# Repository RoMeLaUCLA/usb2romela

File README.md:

# USB2RoMeLa RS-485 USB Adapter

USB2RoMeLa Boosted is a low latency USB to RS-485 adapter. FT232H is used for USB to serial conversion. STM32 intercepts data packets and signals FT232H whenever a complete data packet is received, lowering roundtrip communication latency.
Packet acceleration is designed around Dynamixel communication protocols. 

 ## System Diagram

# Usage

## Baudrate setting

## Terminal resistor setting

## Startup code
 - Flash 2 times: 8Mbps
 - Flash 3 times: 3Mbps
## Error code 
 - Flash 1 time: Packet Timeout
 - Flash 2 times: Checksum Error
 - Flash 3 times: UART Error

# PCB reference

[Link to schematics](/pcb/USB2RoMeLa_Boosted_rev2_1.pdf)

# Latency test

# Folder structure

cad: 3D CAD files and render.

firmware: STM32 firmware with STM32CubeIDE project. \
firmware\Bin: binary file of compiled firmware.

pcb: PCB design files(KiCAD) and schematics. \
pcb\BOM: Bill of Materials. \
pcb\Gerber: PCB mfg files.

tools\ftdi-template: template to use when programing FT232H using FT_Prog.

tools\programming-interface-pcb: PCB design files for interface board with castellation.

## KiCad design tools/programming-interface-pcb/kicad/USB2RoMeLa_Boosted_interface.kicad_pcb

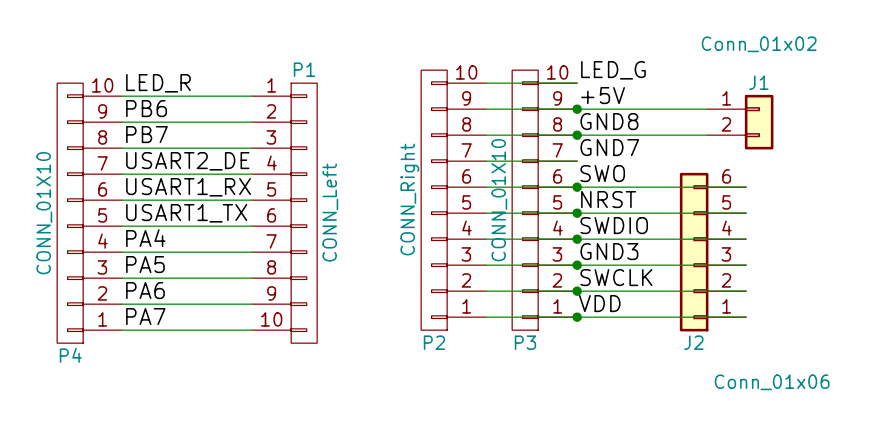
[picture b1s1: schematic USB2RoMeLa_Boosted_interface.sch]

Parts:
J1: Conn_01x02; Molex_MiniFit-JR-5556-02A_2x01x4.20mm_Straight
J2: Conn_01x06; JST_SH_SM06B-SRSS-TB_06x1.00mm_Angled
P1: CONN_Left; Spring_Contact_10P
P2: CONN_Right; Spring_Contact_10P
P3, P4: CONN_01X10; Socket_Strip_Straight_1x10_Pitch2.54mm

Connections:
/+5V: J1.1, P2.9, P3.9
/GND3: J2.3, P2.3, P3.3
/GND7: P2.7, P3.7
/GND8: J1.2, P2.8, P3.8
/LED_G: P2.10, P3.10
/LED_R: P1.1, P4.10
/NRST: J2.5, P2.5, P3.5
/PA4: P1.7, P4.4
/PA5: P1.8, P4.3
/PA6: P1.9, P4.2
/PA7: P1.10, P4.1
/PB6: P1.2, P4.9
/PB7: P1.3, P4.8
/SWCLK: J2.2, P2.2, P3.2
/SWDIO: J2.4, P2.4, P3.4
/SWO: J2.6, P2.6, P3.6
/USART1_RX: P1.5, P4.6
/USART1_TX: P1.6, P4.5
/USART2_DE: P1.4, P4.7
/VDD: J2.1, P2.1, P3.1

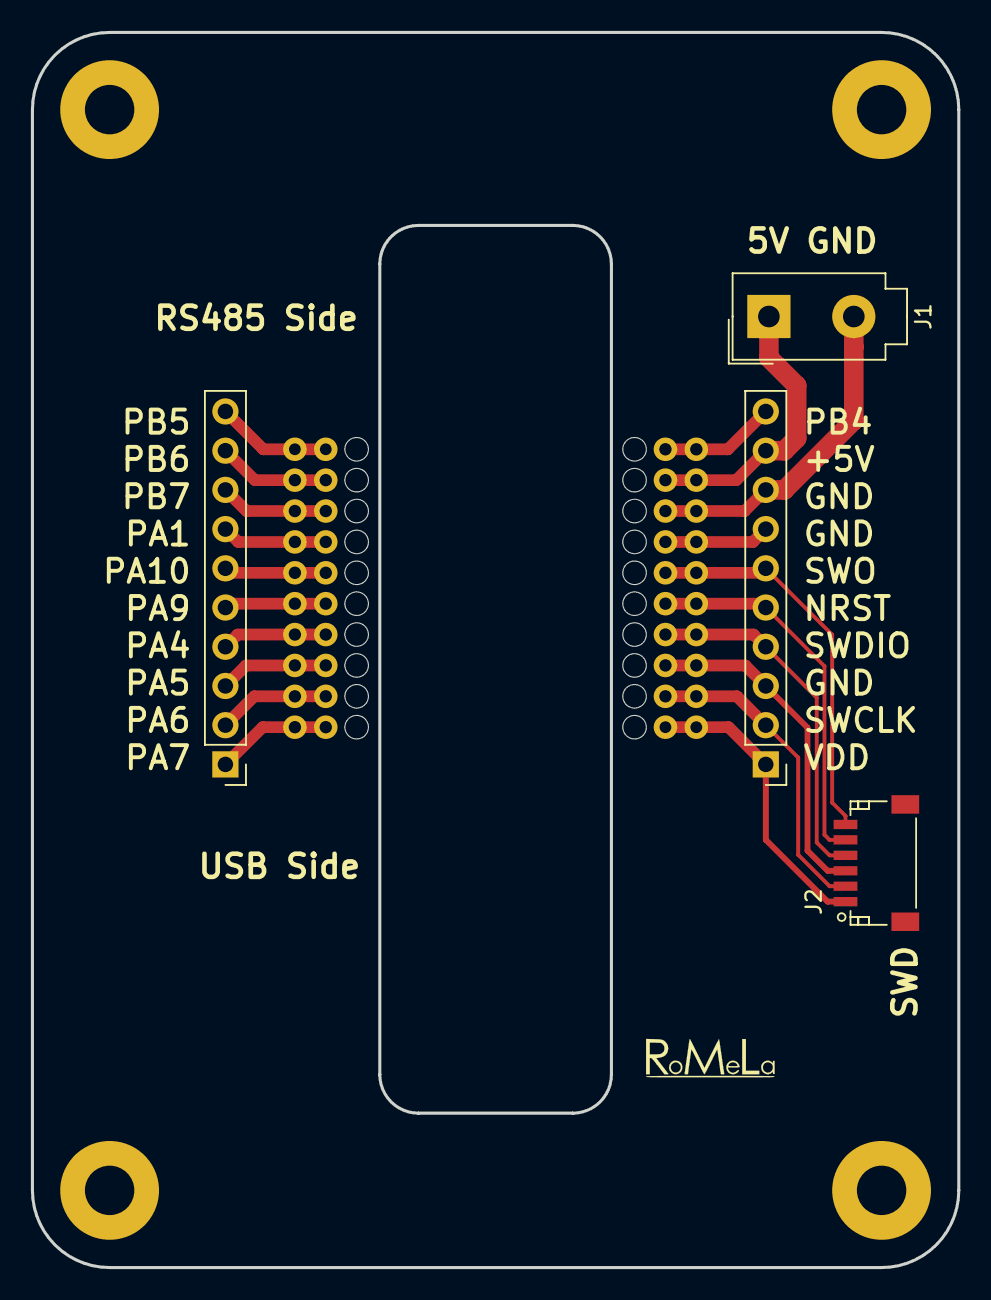
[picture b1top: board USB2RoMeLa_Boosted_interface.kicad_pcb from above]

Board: 2 copper layers, 60.0 x 80.0 mm, 6 parts (0 on the bottom side), 20 nets.

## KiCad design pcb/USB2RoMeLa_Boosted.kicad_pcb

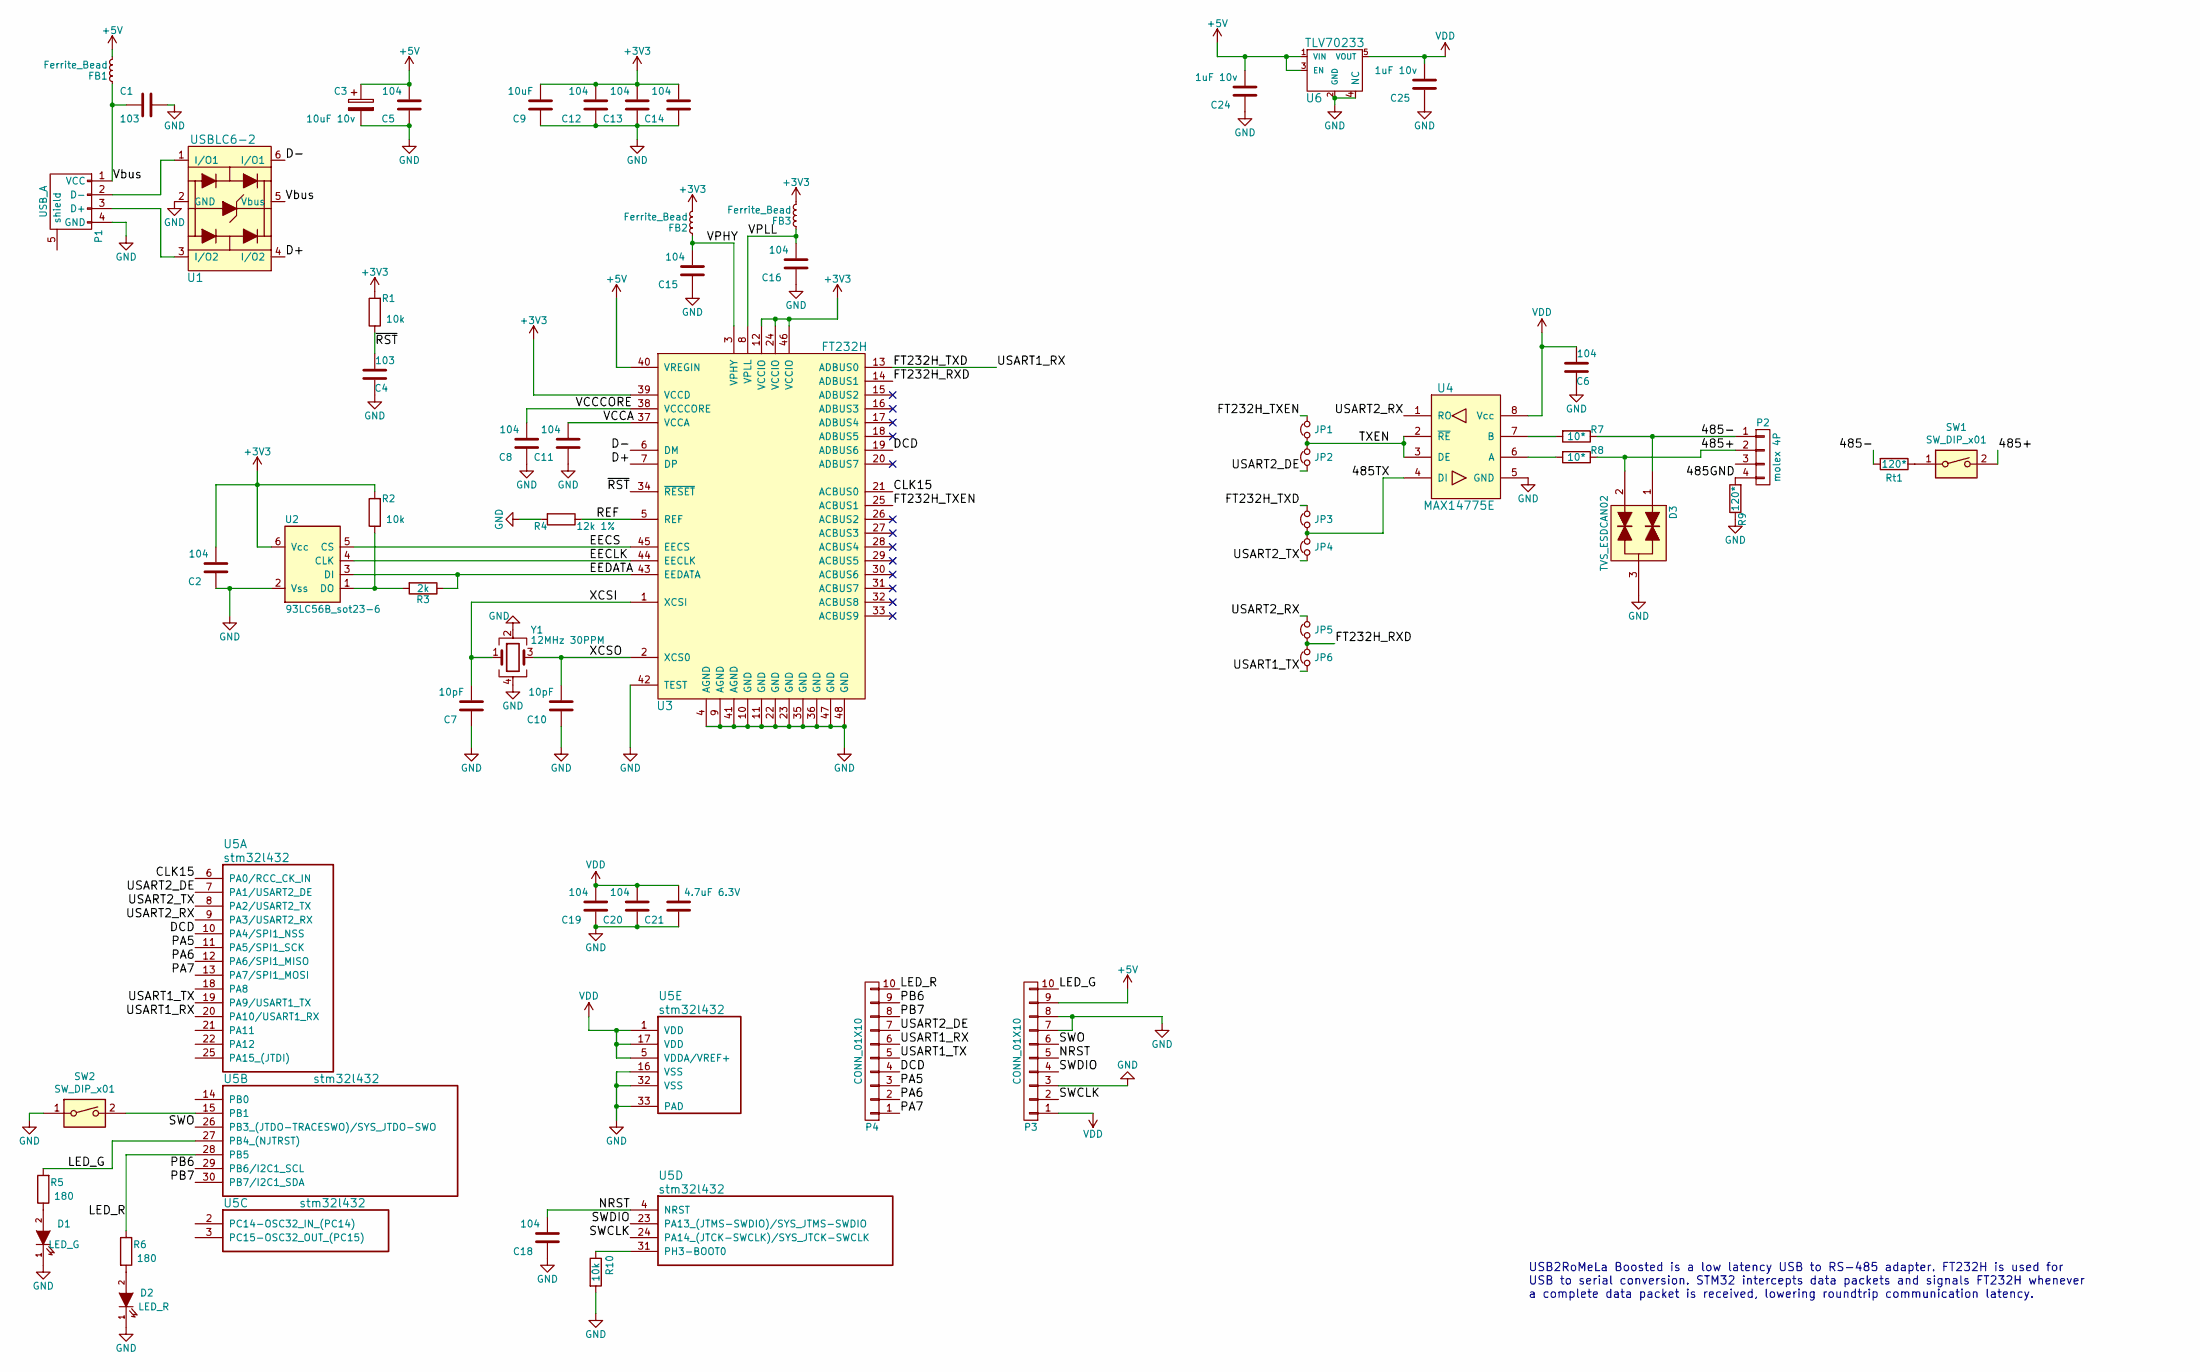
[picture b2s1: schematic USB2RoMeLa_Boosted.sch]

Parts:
C1, C4: 103; C_0402_1005Metric
C2, C5, C6, C8, C11, C12, C13, C14, C15, C16, C18, C19, C20: 104; C_0402_1005Metric
C3: 10uF 10v; C_0805_2012Metric
C7, C10: 10pF; C_0402_1005Metric
C9: 10uF; C_0805_2012Metric
C21: 4.7uF 6.3V; C_0805_2012Metric
C24, C25: 1uF 10v; C_0603_1608Metric
D1: LED_G; LED_0603_1608Metric
D2: LED_R; LED_0603_1608Metric
D3: TVS_ESDCAN02; SOT-323_SC-70
FB1, FB2, FB3: Ferrite_Bead; R_0402_1005Metric
JP1, JP2, JP3, JP4, JP5, JP6: Jumper_NC_Small; R_0402_1005Metric
P1: USB_A; USB_typeA_TH
P2: molex 4P; Molex_4P
P3, P4: CONN_01X10; castellation_10P_2mm
R1, R2, R10: 10k; R_0402_1005Metric
R3: 2k; R_0402_1005Metric
R4: 12k 1%; R_0402_1005Metric
R5, R6: 180; R_0603_1608Metric
R7, R8: 10*; R_0603_1608Metric
R9: 120*; R_0805_2012Metric
Rt1: 120*; R_0805_2012Metric
SW1, SW2: SW_DIP_x01; SW_DIP_SPSTx01_Slide_Copal_CHS-01A_W5.08mm_P1.27mm_JPin
U1: USBLC6-2; SOT-23-6
U2: 93LC56B_sot23-6; SOT-23-6
U3: FT232H; LQFP-48_7x7mm_P0.5mm
U4: MAX14775E; SOIC-8_3.9x4.9mm_P1.27mm
U5: stm32l432; VQFN-32-1EP_5x5mm_P0.5mm_EP3.5x3.5mm
U6: TLV70233; SOT-23-5
Y1: 12MHz 30PPM; Crystal_SMD_2520-4Pin_2.5x2.0mm

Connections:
+3V3: C2.2, C9.2, C12.2, C13.2, C14.2, FB2.2, FB3.2, R1.2, R2.2, U2.6 (Vcc), U3.12 (VCCIO), U3.24 (VCCIO), U3.39 (VCCD), U3.46 (VCCIO)
+5V: C3.1, C5.2, C24.2, FB1.2, P3.9, U3.40 (VREGIN), U6.1 (VIN), U6.3 (EN)
/485+: D3.2, P2.2, R8.1, SW1.2
/485-: D3.1, P2.1, R7.1, Rt1.2
/485GND: P2.4, R9.2
/485TX: JP3.1, JP4.2, U4.4 (DI)
/CLK15: U3.21 (ACBUS0), U5.6 (PA0/RCC_CK_IN)
/D+: U1.4 (I/O2), U3.7 (DP)
/D-: U1.6 (I/O1), U3.6 (DM)
/DCD: P4.4, U3.19 (ADBUS6), U5.10 (PA4/SPI1_NSS)
/EECLK: U2.4 (CLK), U3.44 (EECLK)
/EECS: U2.5 (CS), U3.45 (EECS)
/EEDATA: R3.1, U2.3 (DI), U3.43 (EEDATA)
/FT232H_RXD: JP5.1, JP6.2, U3.14 (ADBUS1)
/FT232H_TXD: JP3.2, P4.6, U3.13 (ADBUS0), U5.20 (PA10/USART1_RX)
/FT232H_TXEN: JP1.2, U3.25 (ACBUS1)
/LED_G: P3.10, R5.2, U5.27 (PB4_(NJTRST))
/LED_R: P4.10, R6.1, U5.28 (PB5)
/NRST: C18.2, P3.5, U5.4 (NRST)
/PA5: P4.3, U5.11 (PA5/SPI1_SCK)
/PA6: P4.2, U5.12 (PA6/SPI1_MISO)
/PA7: P4.1, U5.13 (PA7/SPI1_MOSI)
/PB6: P4.9, U5.29 (PB6/I2C1_SCL)
/PB7: P4.8, U5.30 (PB7/I2C1_SDA)
/REF: R4.1, U3.5 (REF)
/SWCLK: P3.2, U5.24 (PA14_(JTCK-SWCLK)/SYS_JTCK-SWCLK)
/SWDIO: P3.4, U5.23 (PA13_(JTMS-SWDIO)/SYS_JTMS-SWDIO)
/SWO: P3.6, U5.26 (PB3_(JTDO-TRACESWO)/SYS_JTDO-SWO)
/TXEN: JP1.1, JP2.2, U4.2 (~RE), U4.3 (DE)
/USART1_TX: JP6.1, P4.5, U5.19 (PA9/USART1_TX)
/USART2_DE: JP2.1, P4.7, U5.7 (PA1/USART2_DE)
/USART2_RX: JP5.2, U4.1 (RO), U5.9 (PA3/USART2_RX)
/USART2_TX: JP4.1, U5.8 (PA2/USART2_TX)
/VCCA: C11.2, U3.37 (VCCA)
/VCCCORE: C8.2, U3.38 (VCCCORE)
/VPHY: C15.2, FB2.1, U3.3 (VPHY)
/VPLL: C16.2, FB3.1, U3.8 (VPLL)
/Vbus: C1.2, FB1.1, P1.1 (VCC), U1.5 (Vbus)
/XCSI: C7.2, U3.1 (XCSI), Y1.1
/XCSO: C10.2, U3.2 (XCS0), Y1.3
/~RST: C4.2, R1.1, U3.34 (~RESET)
GND: C1.1, C2.1, C3.2, C4.1, C5.1, C6.1, C7.1, C8.1, C9.1, C10.1, C11.1, C12.1, C13.1, C14.1, C15.1, C16.1, C18.1, C19.1, C20.1, C21.1, C24.1, C25.1, D1.1 (K), D2.1 (K), D3.3, P1.4 (GND), P3.3, P3.7, P3.8, R4.2, R9.1, R10.2, SW2.1, U1.2 (GND), U2.2 (Vss), U3.4 (AGND), U3.9 (AGND), U3.10 (GND), U3.11 (GND), U3.22 (GND), U3.23 (GND), U3.35 (GND), U3.36 (GND), U3.41 (AGND), U3.42 (TEST), U3.47 (GND), U3.48 (GND), U4.5 (GND), U5.16 (VSS), U5.32 (VSS), U5.33 (PAD), U6.2 (GND), U6.4 (NC), Y1.2, Y1.4
unnamed: D1.2 (A), R5.1
unnamed: D2.2 (A), R6.2
unnamed: P1.2 (D-), U1.1 (I/O1)
unnamed: P1.3 (D+), U1.3 (I/O2)
unnamed: R2.1, R3.2, U2.1 (DO)
unnamed: R7.2, U4.7 (B)
unnamed: R8.2, U4.6 (A)
unnamed: R10.1, U5.31 (PH3-BOOT0)
unnamed: Rt1.1, SW1.1
unnamed: SW2.2, U5.15 (PB1)
VDD: C6.2, C19.2, C20.2, C21.2, C25.2, P3.1, U4.8 (Vcc), U5.1 (VDD), U5.5 (VDDA/VREF+), U5.17 (VDD), U6.5 (VOUT)

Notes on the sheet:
USB2RoMeLa Boosted is a low latency USB to RS-485 adapter. FT232H is used for USB to serial conversion. STM32 intercepts data packets and signals FT232H whenever a complete data packet is received, lowering roundtrip communication latency.

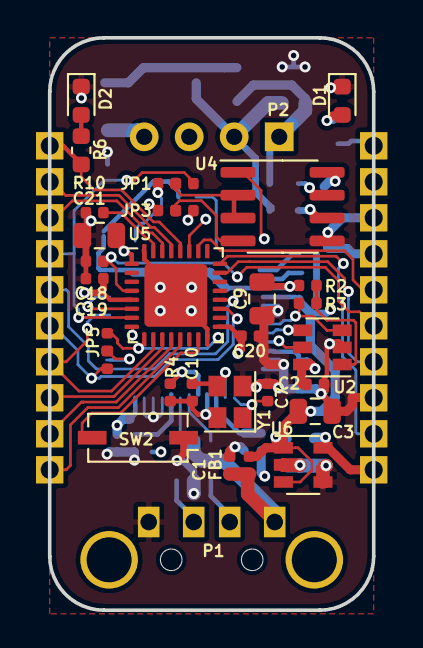
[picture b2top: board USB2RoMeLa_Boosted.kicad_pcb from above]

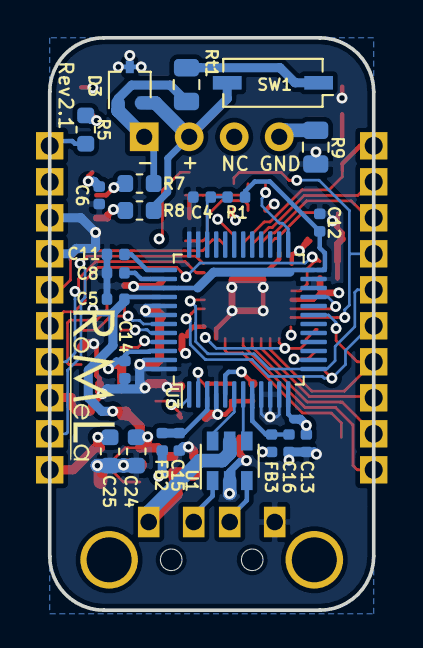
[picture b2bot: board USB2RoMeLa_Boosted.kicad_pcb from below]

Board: 4 copper layers, 18.0 x 31.8 mm, 58 parts (24 on the bottom side), 53 nets.

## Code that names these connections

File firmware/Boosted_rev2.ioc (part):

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Mcu.Name=STM32L432K(B-C)Ux
Mcu.Package=UFQFPN32
Mcu.UserName=STM32L432KCUx
PA0.Mode=HSE-External-Clock-Source-for-LittleOrca
PA0.Signal=RCC_CK_IN
PA10.Mode=Asynchronous
PA10.Signal=USART1_RX
PA13\ (JTMS-SWDIO).Mode=Trace_Asynchronous_SW
PA13\ (JTMS-SWDIO).Signal=SYS_JTMS-SWDIO
PA14\ (JTCK-SWCLK).Mode=Trace_Asynchronous_SW
PA14\ (JTCK-SWCLK).Signal=SYS_JTCK-SWCLK
PA2.Mode=Asynchronous
PA2.Signal=USART2_TX
PA3.Mode=Asynchronous
PA3.Signal=USART2_RX
PA4.GPIOParameters=GPIO_Label
PA4.GPIO_Label=DCD
PA4.Signal=GPIO_Output
PA9.Mode=Asynchronous
PA9.Signal=USART1_TX
PB1.GPIOParameters=GPIO_PuPd,GPIO_Label
PB1.GPIO_Label=SW
PB1.GPIO_PuPd=GPIO_PULLUP
PB1.Signal=GPIO_Input
PB3\ (JTDO-TRACESWO).Mode=Trace_Asynchronous_SW
PB3\ (JTDO-TRACESWO).Signal=SYS_JTDO-SWO
PB4\ (NJTRST).GPIOParameters=GPIO_Label
PB4\ (NJTRST).GPIO_Label=LED_G
PB4\ (NJTRST).Signal=GPIO_Output
PB5.GPIOParameters=GPIO_Label
PB5.GPIO_Label=LED_R
PB5.Signal=GPIO_Output
RCC.HSE_Timout=1000
RCC.HSE_VALUE=15000000
RCC.SYSCLKFreq_VALUE=80000000
RCC.SYSCLKSource=RCC_SYSCLKSOURCE_PLLCLK
board=Boosted_rev2

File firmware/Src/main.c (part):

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	/* Change baudrate based on dip switch position */
	if (BAUD_SW)
	{
		LED_R.Pattern=2;
		HUART_PC.Init.BaudRate = 8000000;
		HUART_MOTOR.Init.BaudRate = 8000000;
	}
	else
	{
		LED_R.Pattern=3;
		HUART_PC.Init.BaudRate = 3000000;
		HUART_MOTOR.Init.BaudRate = 3000000;
	}
	
	LED_R.Cycles=1;
	
	/* UART1 from PC */
	HAL_UART_Init(&HUART_PC);
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  __HAL_RCC_GPIOH_CLK_ENABLE();

  /*Configure GPIO pin Output Level */
  HAL_GPIO_WritePin(DCD_GPIO_Port, DCD_Pin, GPIO_PIN_RESET);

  /*Configure GPIO pin Output Level */
  HAL_GPIO_WritePin(GPIOB, LED_G_Pin|LED_R_Pin, GPIO_PIN_RESET);

  /*Configure GPIO pins : PC14 PC15 */
  GPIO_InitStruct.Pin = GPIO_PIN_14|GPIO_PIN_15;
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  GPIO_InitStruct.Pull = GPIO_NOPULL;
  HAL_GPIO_Init(GPIOC, &GPIO_InitStruct);

  /*Configure GPIO pins : PA1 PA5 PA6 PA7
                           PA8 PA11 PA12 PA15 */
  GPIO_InitStruct.Pin = GPIO_PIN_1|GPIO_PIN_5|GPIO_PIN_6|GPIO_PIN_7
                          |GPIO_PIN_8|GPIO_PIN_11|GPIO_PIN_12|GPIO_PIN_15;
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  GPIO_InitStruct.Pull = GPIO_NOPULL;
  HAL_GPIO_Init(GPIOA, &GPIO_InitStruct);

  /*Configure GPIO pin : DCD_Pin */
  GPIO_InitStruct.Pin = DCD_Pin;
  GPIO_InitStruct.Mode = GPIO_MODE_OUTPUT_PP;
  GPIO_InitStruct.Pull = GPIO_NOPULL;
  GPIO_InitStruct.Speed = GPIO_SPEED_FREQ_LOW;
  HAL_GPIO_Init(DCD_GPIO_Port, &GPIO_InitStruct);

  /*Configure GPIO pins : PB0 PB6 PB7 */
  GPIO_InitStruct.Pin = GPIO_PIN_0|GPIO_PIN_6|GPIO_PIN_7;
  GPIO_InitStruct.Mode = GPIO_MODE_ANALOG;
  GPIO_InitStruct.Pull = GPIO_NOPULL;
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  GPIO_InitStruct.Pull = GPIO_PULLUP;
  HAL_GPIO_Init(SW_GPIO_Port, &GPIO_InitStruct);

  /*Configure GPIO pins : LED_G_Pin LED_R_Pin */
  GPIO_InitStruct.Pin = LED_G_Pin|LED_R_Pin;
  GPIO_InitStruct.Mode = GPIO_MODE_OUTPUT_PP;
  GPIO_InitStruct.Pull = GPIO_NOPULL;
  GPIO_InitStruct.Speed = GPIO_SPEED_FREQ_LOW;
  HAL_GPIO_Init(GPIOB, &GPIO_InitStruct);

  /*Configure GPIO pin : PH3 */
  GPIO_InitStruct.Pin = GPIO_PIN_3;
  GPIO_InitStruct.Mode = GPIO_MODE_ANALOG;
  GPIO_InitStruct.Pull = GPIO_NOPULL;
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	/* Error handling */
	if (Global_Error & ERR_UART)
	{
		LED_G.Pattern = 3;
		LED_G.Cycles = 5;
		Global_Error &= (~ERR_UART);
	}
	else if (Global_Error & ERR_CHECKSUM)
	{
		LED_G.Pattern = 2;
		LED_G.Cycles = 5;
		Global_Error &= (~ERR_CHECKSUM);
	}
	else if (Global_Error & ERR_PACKET_TIMEOUT)
	{
		LED_G.Pattern = 1;
		LED_G.Cycles = 5;
		Global_Error &= (~ERR_PACKET_TIMEOUT);
	}

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
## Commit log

2023-01-12 Firmware added.
2023-01-12 added binary files.
2023-01-13 added PCB files.
2023-01-13 pcb gerber files
2023-01-13 added 3D model.
2023-01-13 added interface pcb. re-organized files.
2025-09-28 add latency plot

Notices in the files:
firmware/Src/main.c:
Copyright (c) 2022 STMicroelectronics.
All rights reserved.
This software is licensed under terms that can be found in the LICENSE file
